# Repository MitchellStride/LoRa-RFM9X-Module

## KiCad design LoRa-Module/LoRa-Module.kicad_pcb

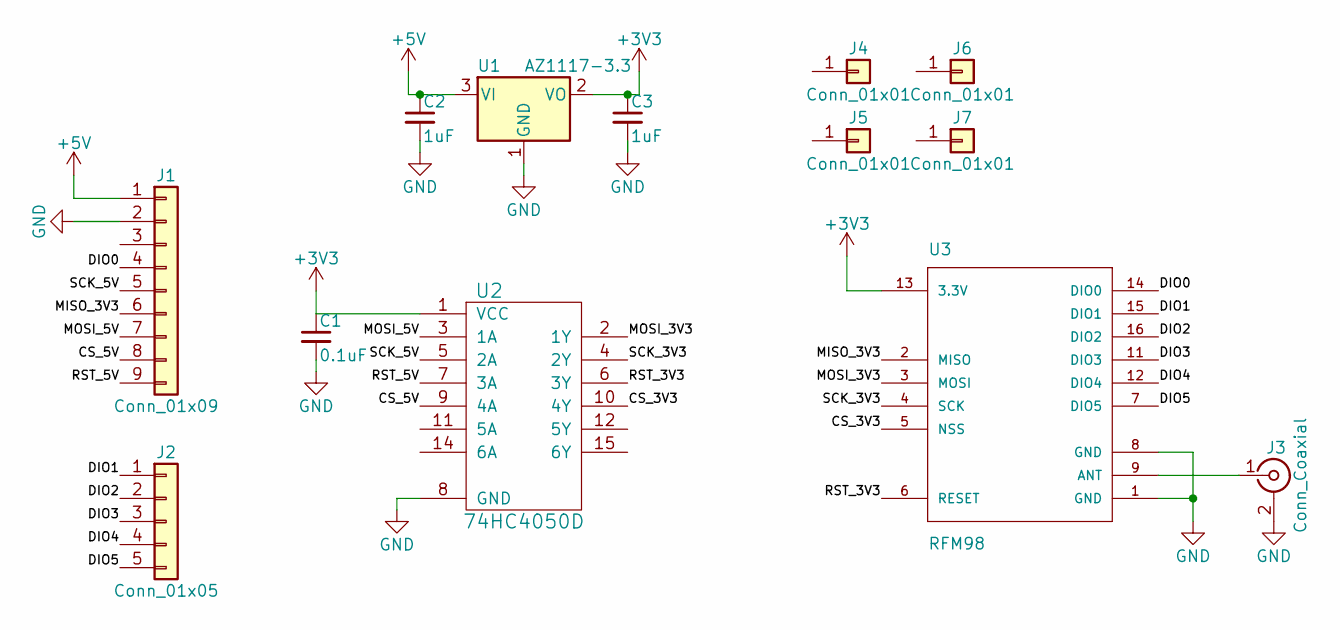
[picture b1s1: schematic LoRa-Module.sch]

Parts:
C1: 0.1uF; C_0603
C2, C3: 1uF; C_0603
J1: Conn_01x09; Pin_Header_Straight_1x09_Pitch2.54mm
J2: Conn_01x05; Pin_Header_Straight_1x05_Pitch2.54mm
J3: Conn_Coaxial; Amphenol_RF_SMA_132289
J4, J5, J6, J7: Conn_01x01; MountingHole_3.2mm_M3
U1: AZ1117-3.3; SOT-223
U2: 74HC4050D; TSSOP-16_4.4x5mm_Pitch0.65mm
U3: RFM98; RFM69HCW-XXXS2

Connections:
+3V3: C1.1, C3.1, U1.2 (VO), U2.1 (VCC), U3.13 (3.3V)
+5V: C2.1, J1.1, U1.3 (VI)
/CS_3V3: U2.10 (4Y), U3.5 (NSS)
/CS_5V: J1.8, U2.9 (4A)
/DIO0: J1.4, U3.14 (DIO0)
/DIO1: J2.1, U3.15 (DIO1)
/DIO2: J2.2, U3.16 (DIO2)
/DIO3: J2.3, U3.11 (DIO3)
/DIO4: J2.4, U3.12 (DIO4)
/DIO5: J2.5, U3.7 (DIO5)
/MISO_3V3: J1.6, U3.2 (MISO)
/MOSI_3V3: U2.2 (1Y), U3.3 (MOSI)
/MOSI_5V: J1.7, U2.3 (1A)
/RST_3V3: U2.6 (3Y), U3.6 (RESET)
/RST_5V: J1.9, U2.7 (3A)
/SCK_3V3: U2.4 (2Y), U3.4 (SCK)
/SCK_5V: J1.5, U2.5 (2A)
GND: C1.2, C2.2, C3.2, J1.2, J3.2 (Ext), U1.1 (GND), U2.8 (GND), U3.1 (GND), U3.8 (GND), U3.10 (GND)
unnamed: J3.1 (In), U3.9 (ANT)

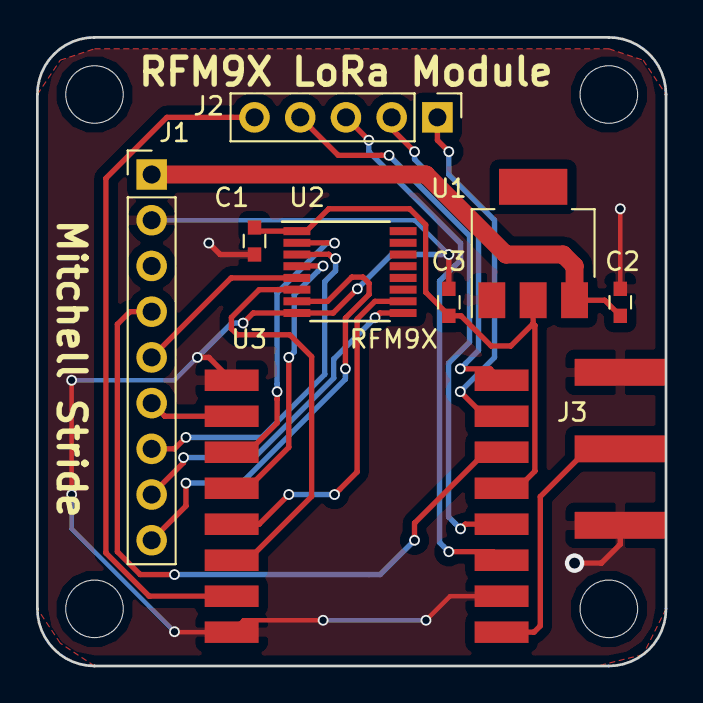
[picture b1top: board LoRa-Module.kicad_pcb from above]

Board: 2 copper layers, 34.9 x 34.9 mm, 13 parts (0 on the bottom side), 19 nets.

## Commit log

2018-05-08 board done and gerbers genned,
2018-05-11 fixed gerber error
2018-05-16 added model and pinout img
2019-11-22 alienware push
